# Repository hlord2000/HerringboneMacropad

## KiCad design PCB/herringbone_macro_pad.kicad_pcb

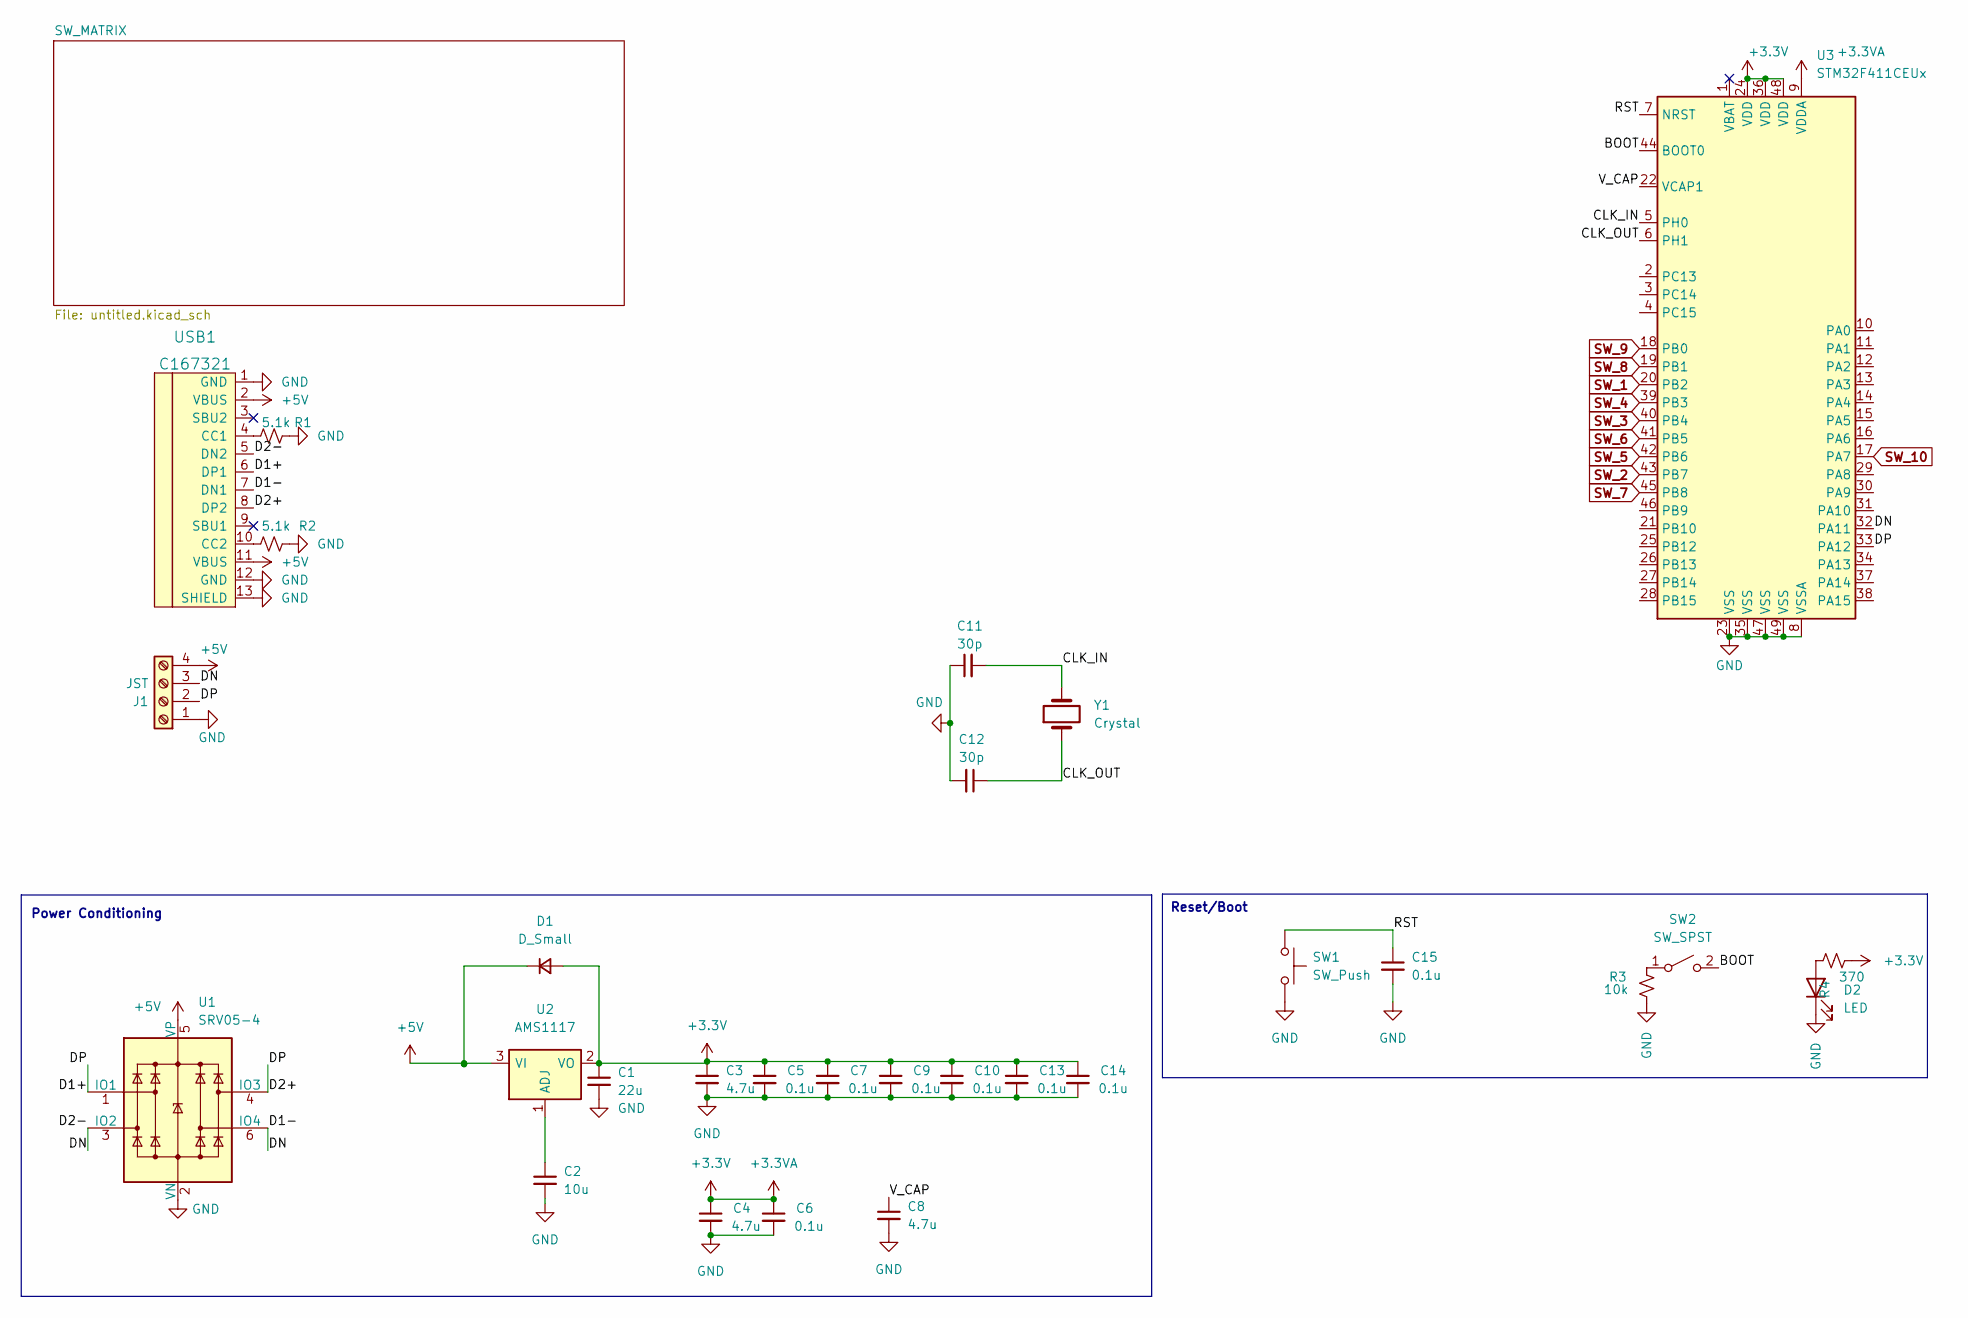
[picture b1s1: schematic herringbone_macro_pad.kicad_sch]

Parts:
C1: 22u; C_0402
C2: 10u; C_0402
C3, C4, C8: 4.7u; C_0402
C5, C6, C7, C9, C10, C13, C14, C15: 0.1u; C_0402
C11, C12: 30p; C_0402
D1: D_Small; D_0805
D2: LED; D_0402_1005Metric
J1: JST; JST_SH_SM04B-SRSS-TB_1x04-1MP_P1.00mm_Horizontal
R1, R2: 5.1k; R_0402
R3: 10k; R_0402
R4: 370; R_0402
SW1: SW_Push; SW_SPST_TL3342
SW2: SW_SPST; SW_SPDT_PCM12
U1: SRV05-4; SOT-23-6
U2: AMS1117; SOT-223-3_TabPin2
U3: STM32F411CEUx; QFN-48-1EP_7x7mm_P0.5mm_EP5.6x5.6mm
USB1: C167321; HRO-TYPE-C-31-M-12-Assembly
Y1: Crystal; Crystal_SMD_0603-2Pin_6.0x3.5mm

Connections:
+3.3VA: C1.1, C3.1, C4.1, C5.1, C6.1, C7.1, C9.1, C10.1, C13.1, C14.1, D1.2 (A), R4.1, U2.2 (VO), U3.9 (VDDA), U3.24 (VDD), U3.36 (VDD), U3.48 (VDD)
+5V: D1.1 (K), J1.4, U1.5 (VP), U2.3 (VI), USB1.2 (VBUS), USB1.11 (VBUS)
/BOOT: SW2.2 (B), U3.44 (BOOT0)
/CLK_IN: C11.2, U3.5 (PH0), Y1.2
/CLK_OUT: C12.1, U3.6 (PH1), Y1.1
/D1+: J1.2, U1.1 (IO1), U1.4 (IO3), U3.33 (PA12), USB1.6 (DP1), USB1.8 (DP2)
/D1-: J1.3, U1.3 (IO2), U1.6 (IO4), U3.32 (PA11), USB1.5 (DN2), USB1.7 (DN1)
/RST: C15.1, SW1.1, U3.7 (NRST)
/V_CAP: C8.1, U3.22 (VCAP1)
GND: C1.2, C2.2, C3.2, C4.2, C5.2, C6.2, C7.2, C8.2, C9.2, C10.2, C11.1, C12.2, C13.2, C14.2, C15.2, D2.1 (K), J1.1, R1.1, R2.1, R3.1, SW1.2, U1.2 (VN), U3.8 (VSSA), U3.23 (VSS), U3.35 (VSS), U3.47 (VSS), U3.49 (VSS), USB1.1 (GND), USB1.12 (GND), USB1.13 (SHIELD); also elsewhere on the board
unnamed: C2.1, U2.1 (ADJ)
unnamed: D2.2 (A), R4.2
unnamed: R1.2, USB1.4 (CC1)
unnamed: R2.2, USB1.10 (CC2)
unnamed: R3.2, SW2.1 (A)
SW_1: U3.20 (PB2); also elsewhere on the board
SW_2: U3.43 (PB7); also elsewhere on the board
SW_3: U3.40 (PB4); also elsewhere on the board
SW_4: U3.39 (PB3); also elsewhere on the board
SW_5: U3.42 (PB6); also elsewhere on the board
SW_6: U3.41 (PB5); also elsewhere on the board
SW_7: U3.45 (PB8); also elsewhere on the board
SW_8: U3.19 (PB1); also elsewhere on the board
SW_9: U3.18 (PB0); also elsewhere on the board
SW_10: U3.17 (PA7); also elsewhere on the board

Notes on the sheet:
Power Conditioning
Reset/Boot

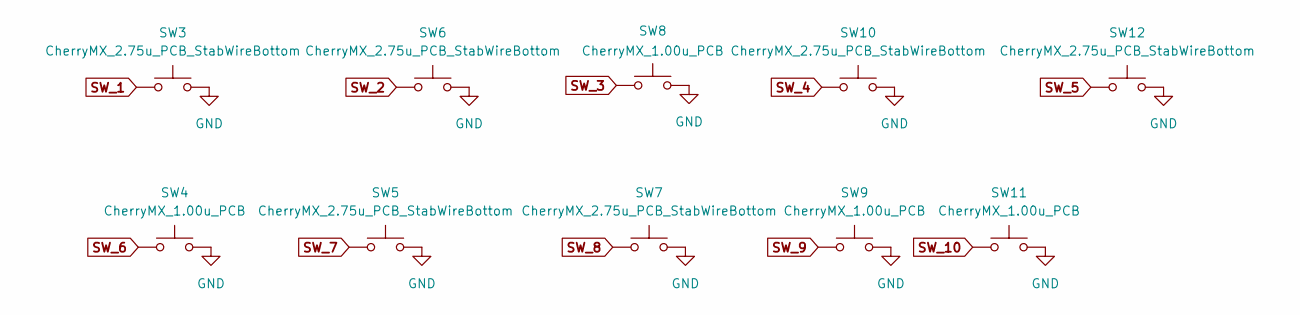
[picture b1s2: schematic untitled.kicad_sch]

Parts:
SW3, SW5, SW6, SW7, SW10, SW12: CherryMX_2.75u_PCB_StabWireBottom; SW_Cherry_MX_2.75u_PCB
SW4, SW8, SW9, SW11: CherryMX_1.00u_PCB; SW_Cherry_MX_1.00u_PCB

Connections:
GND: SW3.2, SW4.2, SW5.2, SW6.2, SW7.2, SW8.2, SW9.2, SW10.2, SW11.2, SW12.2; also elsewhere on the board
SW_1: SW3.1; also elsewhere on the board
SW_2: SW6.1; also elsewhere on the board
SW_3: SW8.1; also elsewhere on the board
SW_4: SW10.1; also elsewhere on the board
SW_5: SW12.1; also elsewhere on the board
SW_6: SW4.1; also elsewhere on the board
SW_7: SW5.1; also elsewhere on the board
SW_8: SW7.1; also elsewhere on the board
SW_9: SW9.1; also elsewhere on the board
SW_10: SW11.1; also elsewhere on the board

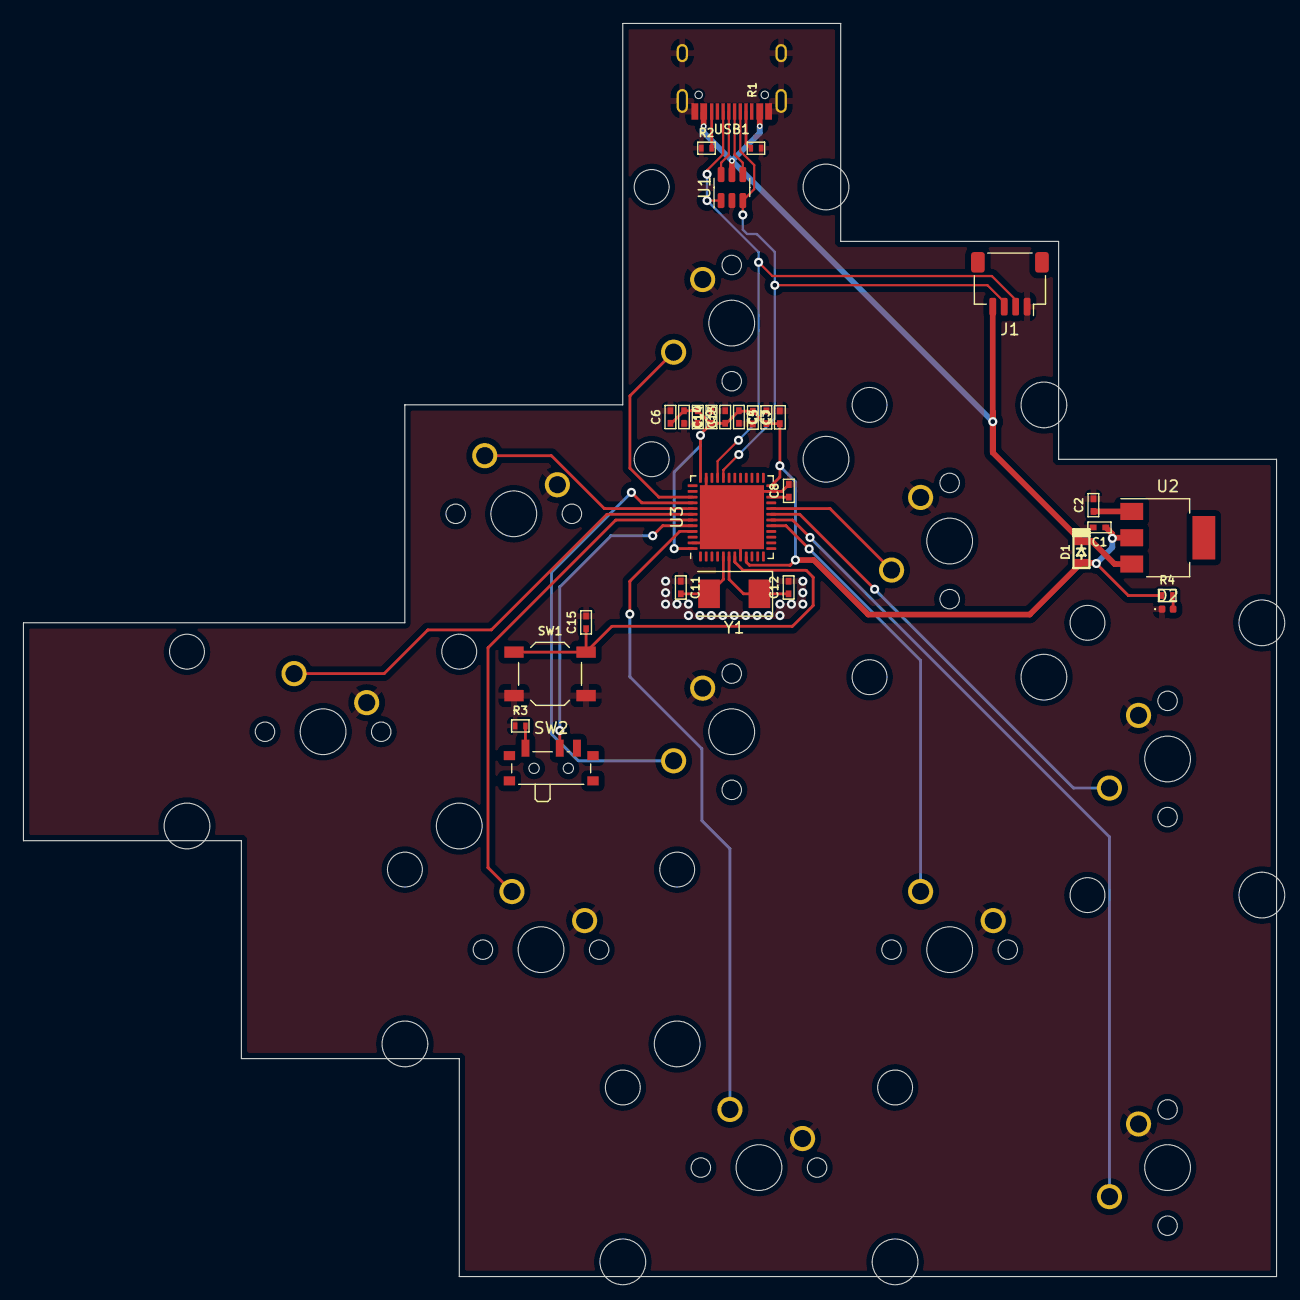
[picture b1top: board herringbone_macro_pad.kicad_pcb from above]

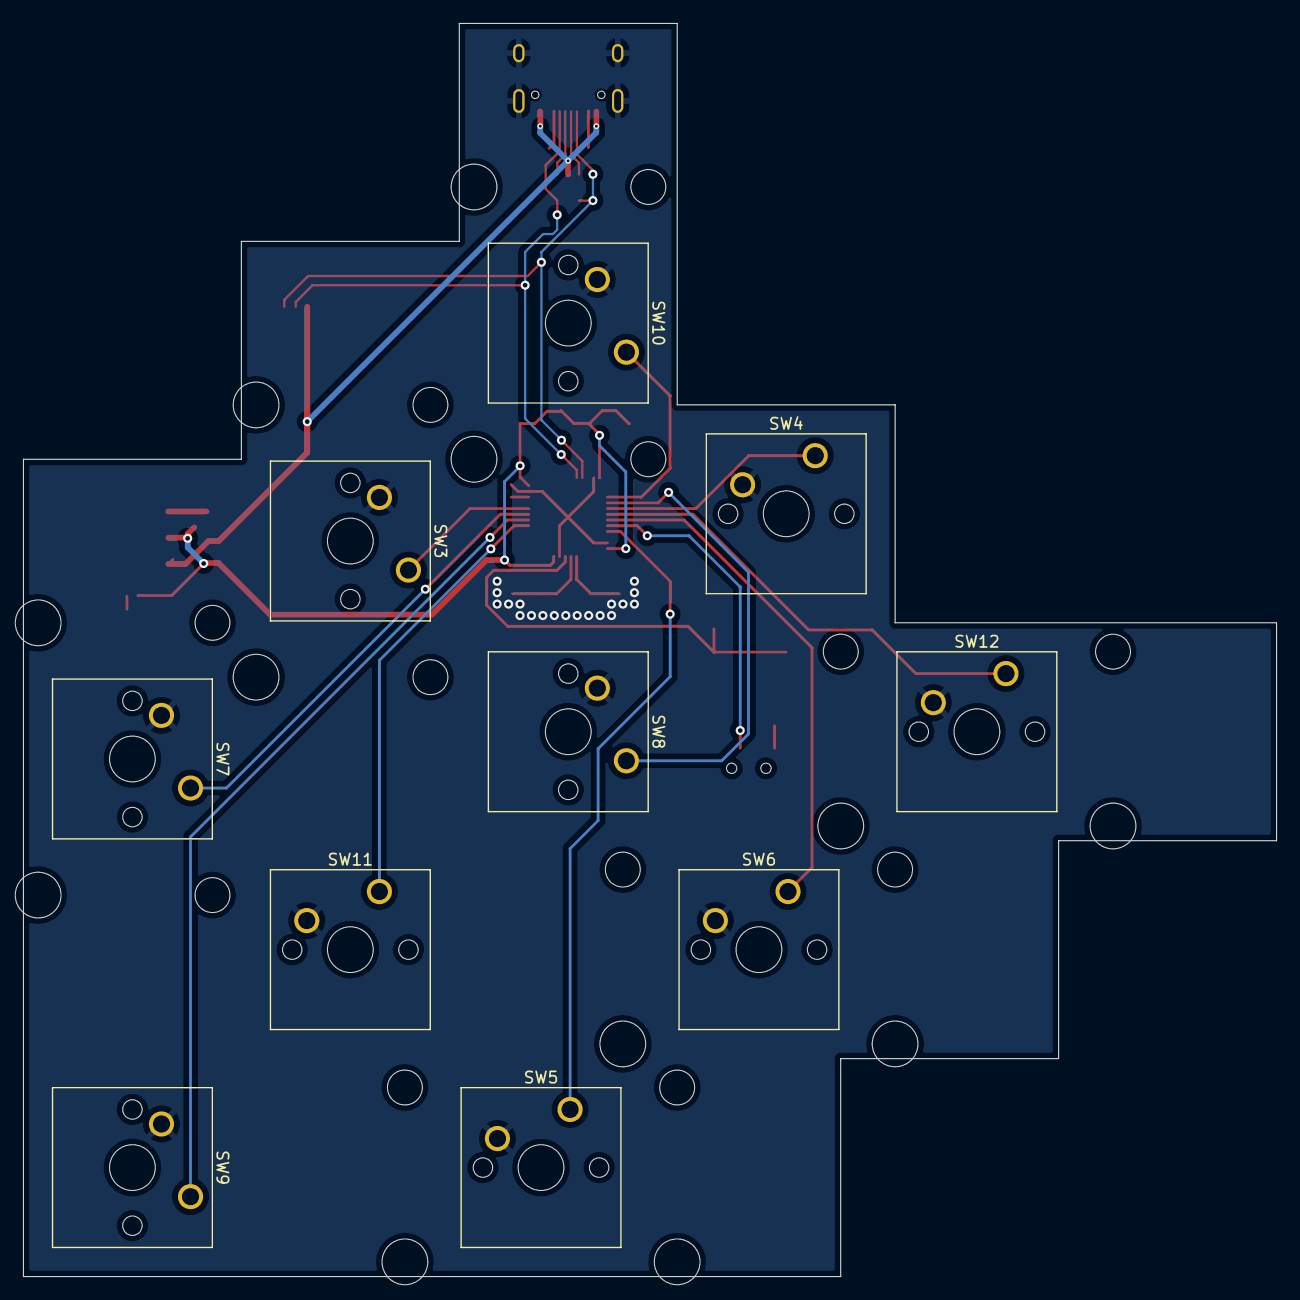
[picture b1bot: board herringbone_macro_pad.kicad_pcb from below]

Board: 2 copper layers, 109.5 x 109.5 mm, 39 parts (10 on the bottom side), 25 nets.

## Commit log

2022-02-12 Initial commit.
2022-02-12 restructured files
2022-02-16 update, hardware rev 2.0
2022-02-18 Hardware revision.
2022-02-18 Hardware revision 2/17/2022
